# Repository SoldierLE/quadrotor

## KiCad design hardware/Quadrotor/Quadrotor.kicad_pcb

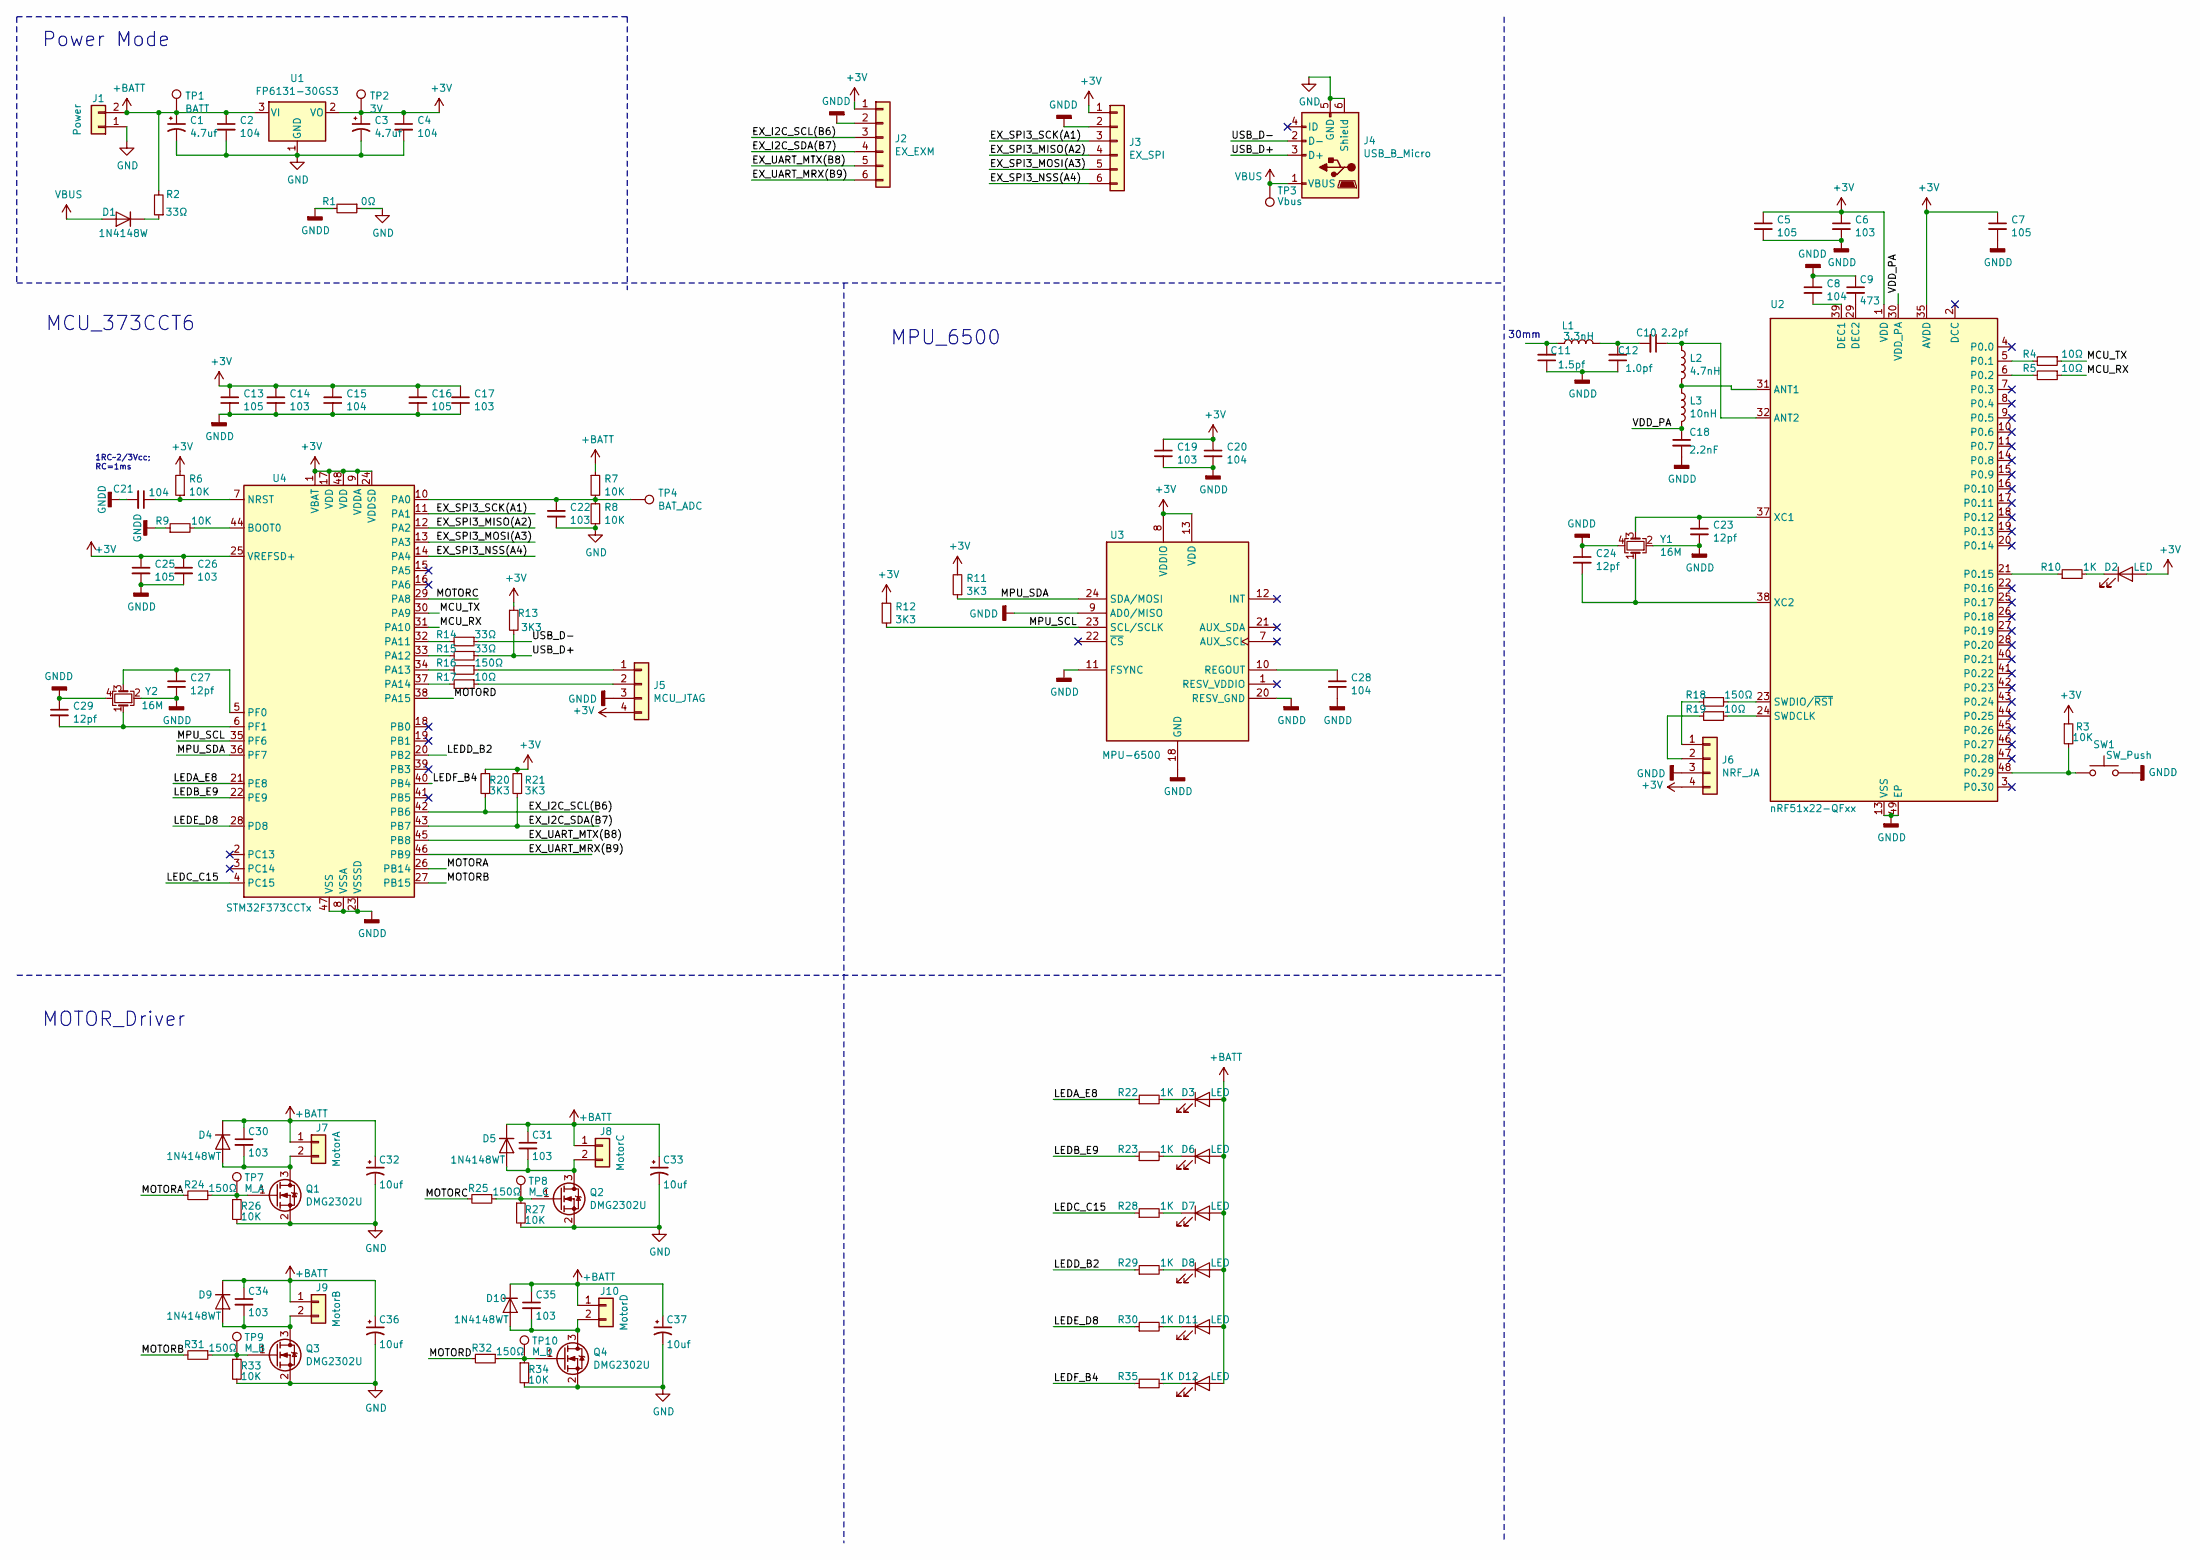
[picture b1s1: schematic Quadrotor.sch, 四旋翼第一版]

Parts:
C1, C3: 4.7uf; C_0603_1608Metric_Pad1.05x0.95mm_HandSolder
C2, C4, C8, C15, C20, C21, C28: 104; C_0402_1005Metric
C5, C7, C13, C16, C25: 105; C_0402_1005Metric
C6, C14, C17, C19, C22, C26, C30, C31, C34, C35: 103; C_0402_1005Metric
C9: 473; C_0402_1005Metric
C10: 2.2pf; C_0402_1005Metric
C11: 1.5pf; C_0402_1005Metric
C12: 1.0pf; C_0402_1005Metric
C18: 2.2nF; C_0402_1005Metric
C23, C24, C27, C29: 12pf; C_0402_1005Metric
C32, C33, C36, C37: 10uf; C_0805_2012Metric_Pad1.15x1.40mm_HandSolder
D1: 1N4148W; D_PowerDI-123
D2, D3, D6, D7, D8, D11, D12: LED; D_0603_1608Metric_Pad1.05x0.95mm_HandSolder
D4, D5, D9, D10: 1N4148WT; D_SOD-523
J1: Power; PinHeader_1x02_P2.54mm_Vertical
J2: EX_EXM; PinHeader_1x06_P2.00mm_Vertical
J3: EX_SPI; PinHeader_1x06_P2.00mm_Vertical
J4: USB_B_Micro; USB_Micro-B_Molex-105017-0001
J5: MCU_JTAG; PinHeader_1x04_P2.54mm_Vertical
J6: NRF_JA; PinHeader_1x04_P2.54mm_Vertical
J7: MotorA; MOTOR
J8: MotorC; MOTOR
J9: MotorB; MOTOR
J10: MotorD; MOTOR
L1: 3.3nH; L_0402_1005Metric
L2: 4.7nH; L_0402_1005Metric
L3: 10nH; L_0402_1005Metric
Q1, Q2, Q3, Q4: DMG2302U; SOT-23
R1: 0Ω; R_0805_2012Metric_Pad1.15x1.40mm_HandSolder
R2, R14, R15: 33Ω; R_0402_1005Metric
R3, R6, R7, R8, R9, R26, R27, R33, R34: 10K; R_0402_1005Metric
R4, R5, R17, R19: 10Ω; R_0402_1005Metric
R10, R22, R23, R28, R29, R30, R35: 1K; R_0402_1005Metric
R11, R12, R13, R20, R21: 3K3; R_0402_1005Metric
R16, R18, R24, R25, R31, R32: 150Ω; R_0402_1005Metric
SW1: SW_Push; SW_SPST_PTS810
TP1: BATT; TestPoint_Pad_D1.5mm
TP2: 3V; TestPoint_Pad_D1.5mm
TP3: Vbus; TestPoint_Pad_D1.5mm
TP4: BAT_ADC; TestPoint_Pad_D1.0mm
TP7: M_A; TestPoint_Pad_D1.5mm
TP8: M_C; TestPoint_Pad_D1.5mm
TP9: M_B; TestPoint_Pad_D1.5mm
TP10: M_D; TestPoint_Pad_D1.5mm
U1: FP6131-30GS3; SOT-23
U2: nRF51x22-QFxx; QFN-48-1EP_6x6mm_P0.4mm_EP4.6x4.6mm
U3: MPU-6500; InvenSense_QFN-24_3x3mm_P0.4mm
U4: STM32F373CCTx; LQFP-48_7x7mm_P0.5mm
Y1, Y2: 16M; Oscillator_SMD_EuroQuartz_XO32-4Pin_3.2x2.5mm_HandSoldering

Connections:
+3V3: C3.1, C4.1, C5.1, C6.1, C7.1, C13.1, C14.1, C15.1, C16.1, C17.1, C19.1, C20.1, C25.1, C26.1, D2.2 (A), J2.1, J3.1, J5.4, J6.4, R3.1, R6.2, R11.2, R12.1, R13.1, R20.2, R21.2, TP2.1, U1.2 (VO), U2.1 (VDD), U2.12 (VDD), U2.35 (AVDD), U2.36 (AVDD), U3.8 (VDDIO), U3.13 (VDD), U4.1 (VBAT), U4.9 (VDDA), U4.17 (VDD), U4.24 (VDDSD), U4.25 (VREFSD+), U4.48 (VDD)
+BATT: C1.1, C2.1, C30.1, C31.1, C32.1, C33.1, C34.1, C35.1, C36.1, C37.1, D3.2 (A), D4.1 (K), D5.1 (K), D6.2 (A), D7.2 (A), D8.2 (A), D9.1 (K), D10.1 (K), D11.2 (A), D12.2 (A), J1.2, J7.1, J8.1, J9.1, J10.1, R2.2, R7.1, TP1.1, U1.3 (VI)
/EX_I2C_SCL(B6): J2.3, R20.1, U4.42 (PB6)
/EX_I2C_SDA(B7): J2.4, R21.1, U4.43 (PB7)
/EX_SPI3_MISO(A2): J3.4, U4.12 (PA2)
/EX_SPI3_MOSI(A3): J3.5, U4.13 (PA3)
/EX_SPI3_NSS(A4): J3.6, U4.14 (PA4)
/EX_SPI3_SCK(A1): J3.3, U4.11 (PA1)
/EX_UART_MRX(B9): J2.6, U4.46 (PB9)
/EX_UART_MTX(B8): J2.5, U4.45 (PB8)
/LEDA_E8: R22.1, U4.21 (PE8)
/LEDB_E9: R23.1, U4.22 (PE9)
/LEDC_C15: R28.1, U4.4 (PC15)
/LEDD_B2: R29.1, U4.20 (PB2)
/LEDE_D8: R30.1, U4.28 (PD8)
/LEDF_B4: R35.1, U4.40 (PB4)
/MCU_RX: R5.1, U4.31 (PA10)
/MCU_TX: R4.1, U4.30 (PA9)
/MOTORA: R24.2, U4.26 (PB14)
/MOTORB: R31.2, U4.27 (PB15)
/MOTORC: R25.2, U4.29 (PA8)
/MOTORD: R32.2, U4.38 (PA15)
/MPU_SCL: R12.2, U3.23 (SCL/SCLK), U4.35 (PF6)
/MPU_SDA: R11.1, U3.24 (SDA/MOSI), U4.36 (PF7)
/USB_D+: J4.3 (D+), R13.2, R15.1
/USB_D-: J4.2 (D-), R14.1
/VDD_PA: C18.1, L3.2, U2.30 (VDD_PA)
GND: C1.2, C2.2, C3.2, C4.2, C22.2, C32.2, C33.2, C36.2, C37.2, J1.1, J4.5 (GND), J4.6 (Shield), Q1.2 (S), Q2.2 (S), Q3.2 (S), Q4.2 (S), R1.1, R8.1, R26.2, R27.2, R33.2, R34.2, U1.1 (GND)
GNDD: C5.2, C6.2, C7.2, C8.1, C9.1, C11.1, C12.1, C13.2, C14.2, C15.2, C16.2, C17.2, C18.2, C19.2, C20.2, C21.2, C23.2, C24.1, C25.2, C26.2, C27.2, C28.2, C29.1, J2.2, J3.2, J5.3, J6.3, R1.2, R9.1, SW1.2, U2.13 (VSS), U2.33 (VSS), U2.34 (VSS), U2.49 (EP), U3.9 (AD0/MISO), U3.11 (FSYNC), U3.18 (GND), U3.20 (RESV_GND), U4.8 (VSSA), U4.23 (VSSSD), U4.47 (VSS), Y1.2, Y1.4, Y2.2, Y2.4
unnamed: C8.2, U2.39 (DEC1)
unnamed: C9.2, U2.29 (DEC2)
unnamed: C10.1, L2.1, U2.32 (ANT2)
unnamed: C10.2, C12.2, L1.2
unnamed: C11.2, L1.1
unnamed: C21.1, R6.1, U4.7 (NRST)
unnamed: C22.1, R7.2, R8.2, TP4.1, U4.10 (PA0)
unnamed: C23.1, U2.37 (XC1), Y1.3
unnamed: C24.2, U2.38 (XC2), Y1.1
unnamed: C27.1, U4.5 (PF0), Y2.3
unnamed: C28.1, U3.10 (REGOUT)
unnamed: C29.2, U4.6 (PF1), Y2.1
unnamed: C30.2, D4.2 (A), J7.2, Q1.3 (D)
unnamed: C31.2, D5.2 (A), J8.2, Q2.3 (D)
unnamed: C34.2, D9.2 (A), J9.2, Q3.3 (D)
unnamed: C35.2, D10.2 (A), J10.2, Q4.3 (D)
unnamed: D1.1 (K), R2.1
unnamed: D2.1 (K), R10.2
unnamed: D3.1 (K), R22.2
unnamed: D6.1 (K), R23.2
unnamed: D7.1 (K), R28.2
unnamed: D8.1 (K), R29.2
unnamed: D11.1 (K), R30.2
unnamed: D12.1 (K), R35.2
unnamed: J5.1, R16.1
unnamed: J5.2, R17.1
unnamed: J6.1, R18.2
unnamed: J6.2, R19.2
unnamed: L2.2, L3.1, U2.31 (ANT1)
unnamed: Q1.1 (G), R24.1, R26.1, TP7.1
unnamed: Q2.1 (G), R25.1, R27.1, TP8.1
unnamed: Q3.1 (G), R31.1, R33.1, TP9.1
unnamed: Q4.1 (G), R32.1, R34.1, TP10.1
unnamed: R3.2, SW1.1, U2.48 (P0.29)
unnamed: R4.2, U2.5 (P0.1)
unnamed: R5.2, U2.6 (P0.2)
unnamed: R9.2, U4.44 (BOOT0)
unnamed: R10.1, U2.21 (P0.15)
unnamed: R14.2, U4.32 (PA11)
unnamed: R15.2, U4.33 (PA12)
unnamed: R16.2, U4.34 (PA13)
unnamed: R17.2, U4.37 (PA14)
unnamed: R18.1, U2.23 (SWDIO/~RST)
unnamed: R19.1, U2.24 (SWDCLK)
VBUS: D1.2 (A), J4.1 (VBUS), TP3.1

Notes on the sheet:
30mm
Power Mode
1RC~~2/3Vcc; RC=1ms
MOTOR_Driver
MCU_373CCT6
MPU_6500

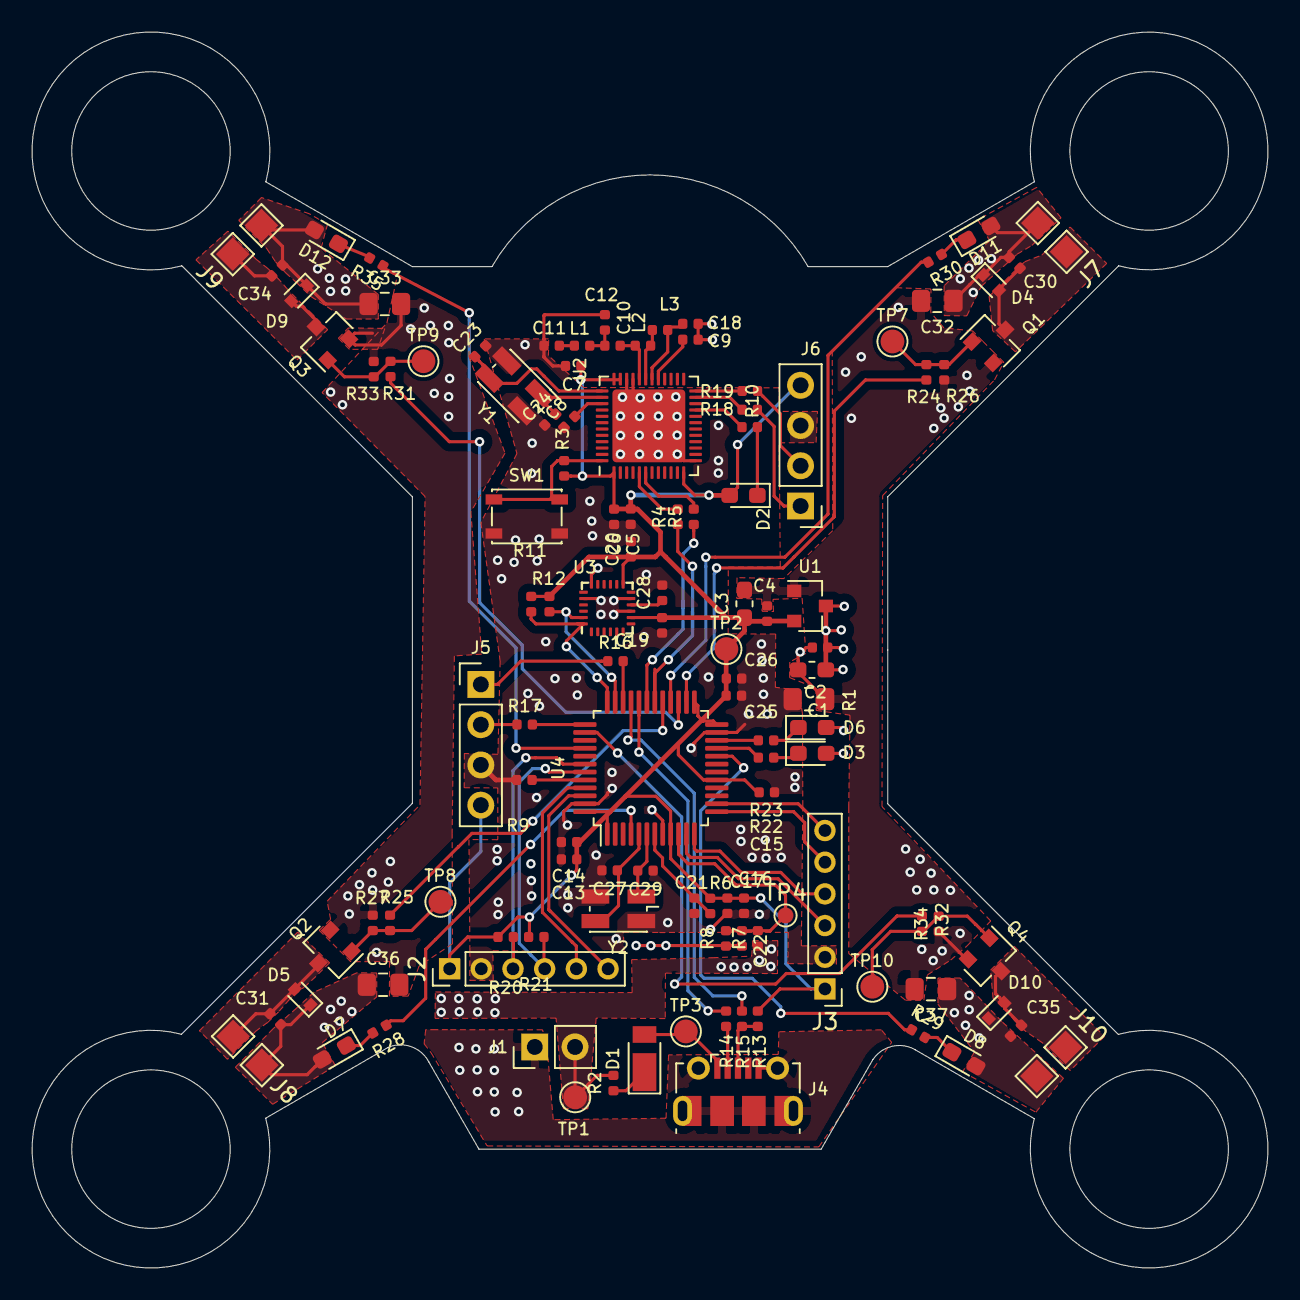
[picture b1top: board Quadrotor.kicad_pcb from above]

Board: 2 copper layers, 78.0 x 78.0 mm, 116 parts (0 on the bottom side), 74 nets.

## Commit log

2020-02-10 update sch and pcb,pcb layout is updating
2020-03-01 PCB布板完成
2020-03-01 添加一点覆铜地
